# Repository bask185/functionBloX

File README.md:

# Function block programming 4 Arduinoy

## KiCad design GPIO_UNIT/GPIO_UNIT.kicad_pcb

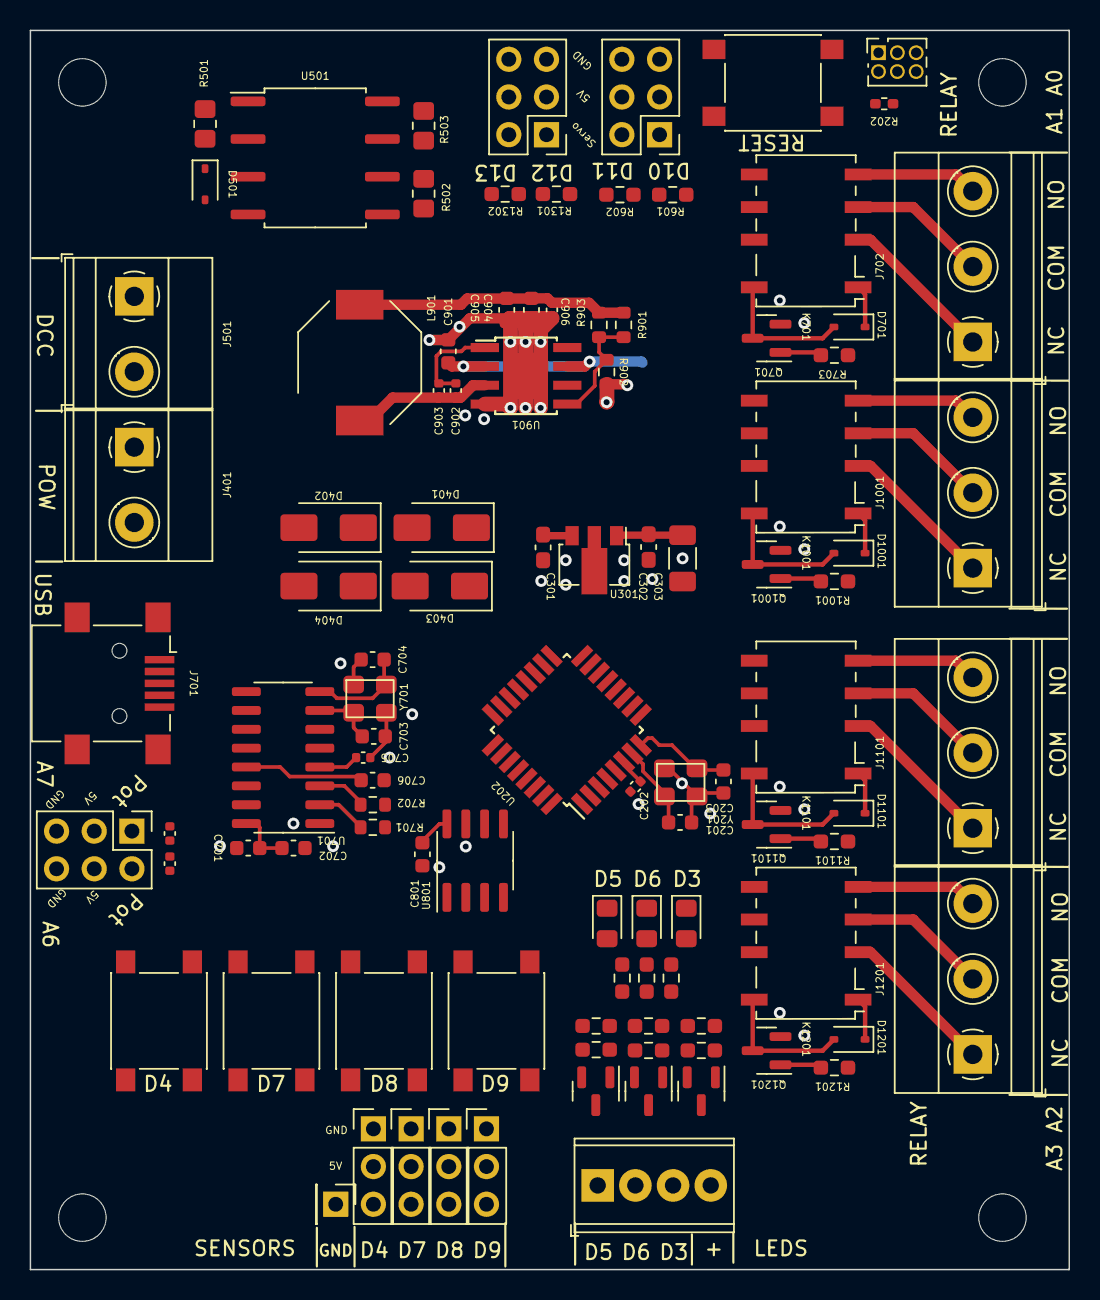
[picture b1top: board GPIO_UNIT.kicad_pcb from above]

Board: 2 copper layers, 70.0 x 83.5 mm, 101 parts (0 on the bottom side), 75 nets.

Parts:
C201, C203: 12pF; C_0603_1608Metric
C202, C705, C902, C906, C1401, C1402: 100nF; C_0402_1005Metric
C301: 330nF; C_0603_1608Metric_Pad1.08x0.95mm_HandSolder
C302: 100nF; C_0603_1608Metric_Pad1.08x0.95mm_HandSolder
C303: 100uF; C_1206_3216Metric_Pad1.33x1.80mm_HandSolder
C701: 10uF; C_0603_1608Metric
C702, C706, C801: 100nF; C_0603_1608Metric
C703, C704: 22pF; C_0603_1608Metric
C901, C904, C905: 22uF; C_0603_1608Metric
C903: 22nF; C_0402_1005Metric
D401, D402, D403, D404: SS53; D_SMA
D501, D701, D1001, D1101, D1201: 1N4148WS; D_SOD-323
D901, D902, D903: LED; LED_0805_2012Metric_Pad1.15x1.40mm_HandSolder
J401, J501: Screw_Terminal_01x02; TerminalBlock_Phoenix_MKDS-1,5-2-5.08_1x02_P5.08mm_Horizont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
J601, J1301, J1401: Conn_02x03_Odd_Even; PinHeader_2x03_P2.54mm_Vertical
J701: USB_B_Mini; USB_Mini-B_Lumberg_2486_01_Horizontal
J702, J1001, J1101, J1201: Screw_Terminal_01x03; TerminalBlock_Phoenix_MKDS-1,5-3-5.08_1x03_P5.08mm_Horizont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
J802, J803, J804, J805: Conn_01x03_Pin; PinHeader_1x03_P2.54mm_Vertical
J806: Conn_01x01_Pin; PinHeader_1x01_P2.54mm_Vertical
J901: Screw_Terminal_01x04; TerminalBlock_Phoenix_MPT-0,5-4-2.54_1x04_P2.54mm_Horizontal
K701, K1001, K1101, K1201: G6K-2F-Y-TR DC5; Relay_DPDT_Omron_G6K-2F-Y
L901: L; L_Bourns-SRU8028_8.0x8.0mm
Q701, Q1001, Q1101, Q1201: NPN_TOR; SOT-23
Q901, Q902, Q903: AO3400A; SOT-23
R202: 10k; R_0402_1005Metric_Pad0.72x0.64mm_HandSolder
R501: 1k; R_0805_2012Metric_Pad1.20x1.40mm_HandSolder
R502, R503: 10k; R_0805_2012Metric_Pad1.20x1.40mm_HandSolder
R601, R602, R1301, R1302: 10k; R_0603_smalltext
R701, R702: 1k; R_0603_1608Metric
R703, R1001, R1101, R1201: 1k; R_0603_smalltext
R901: 220k; R_0603_1608Metric
R902: 20k; R_0603_1608Metric
R903: 150k; R_0603_1608Metric
R904, R905, R906: 22R; R_0603_smalltext
R907, R908, R909: 3k3; R_0603_smalltext
R910, R911, R912: 22k; R_0603_smalltext
SW202, SW801, SW802, SW803, SW804: SW_Push; tactile_SMD_6mm
U201: HEADER_3x2; PinSocket_2x03_P1.27mm_Vertical
U202: ATmega328-A; TQFP-32_7x7mm_P0.8mm
U301: L78L05_SOT89; SOT-89-3
U501: 6N137; SOP-8_6.62x9.15mm_P2.54mm
U701: CH340G; SOIC-16_3.9x9.9mm_P1.27mm
U801: 24LC256; SOIC-8_3.9x4.9mm_P1.27mm
U901: MT2499A; TI_SO-PowerPAD-8
Y201: Crystal_GND2; crystal_arduino
Y701: Crystal; crystal_arduino

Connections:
+5V: C202.1, C302.1, C303.1, C701.1, C702.1, C801.2, C1401.1, C1402.2, J701.1 (VBUS), J802.2, J803.2, J804.2, J805.2, J1401.3, J1401.4, R202.1, R502.1, R503.1, R601.2, R602.2, R1301.2, R1302.2, U201.5, U202.4 (VCC), U202.6 (VCC), U202.18 (AVCC), U301.1 (OUT), U501.8 (VCC), U701.16 (VCC), U801.8 (VCC)
+5VA: C904.1, C905.1, C906.1, D701.1 (K), D1001.1 (K), D1101.1 (K), D1201.1 (K), J601.3, J601.4, J1301.3, J1301.4, K701.1, K1001.1, K1101.1, K1201.1, L901.2, R901.1, R903.2
/CPU/X1: C201.2, U202.7 (XTAL1/PB6), Y201.1
/CPU/X2: C203.2, U202.8 (XTAL2/PB7), Y201.3
/DCC: R503.2, U202.32 (PD2), U501.6 (VO)
/L1: R904.1, R907.2, U202.1 (PD3)
/L2: R905.1, R908.2, U202.9 (PD5)
/L3: R906.1, R909.2, U202.10 (PD6)
/P1: C1402.1, J1401.2, U202.19 (ADC6), U202.22 (ADC7)
/P2: C1401.2, J1401.1
/R1: R703.1, U202.23 (PC0)
/R2: R1001.1, U202.24 (PC1)
/R3: R1101.1, U202.25 (PC2)
/R4: R1201.1, U202.26 (PC3)
/Rx: R701.2, U202.30 (PD0)
/S1: J601.1, R601.1, U202.14 (PB2)
/S2: J601.2, R602.1, U201.3, U202.15 (PB3)
/S3: J1301.1, R1301.1, U201.6, U202.16 (PB4)
/S4: J1301.2, R1302.1, U201.4, U202.17 (PB5)
/SCL: U202.28 (PC5), U801.6 (SCL)
/SDA: U202.27 (PC4), U801.5 (SDA)
/SW1: J802.3, SW801.1, U202.2 (PD4)
/SW2: J803.3, SW802.1, U202.11 (PD7)
/SW3: J804.3, SW803.1, U202.12 (PB0)
/SW4: J805.3, SW804.1, U202.13 (PB1)
/Tx: R702.1, U202.31 (PD1)
/reset: C706.2, R202.2, SW202.2, U201.2
GND: C201.1, C202.2, C203.1, C301.2, C302.2, C303.2, C701.2, C702.2, C703.2, C704.2, C705.1, C801.1, C901.2, C904.2, C905.2, C906.2, D402.2 (A), D404.2 (A), D901.1 (K), D902.1 (K), D903.1 (K), J601.5, J601.6, J701.5 (GND), J701.6 (Shield), J802.1, J803.1, J804.1, J805.1, J806.1, J1301.5, J1301.6, J1401.5, J1401.6, Q701.2 (E), Q901.2 (S), Q902.2 (S), Q903.2 (S), Q1001.2 (E), Q1101.2 (E), Q1201.2 (E), R902.2, R910.2, R911.2, R912.2, SW202.1, SW801.2, SW802.2, SW803.2, SW804.2, U201.1, U202.3 (GND), U202.5 (GND), U202.21 (GND), U301.2 (GND), U501.5 (GND), U701.1 (GND), U801.1 (A0), U801.2 (A1), U801.3 (A2), U801.4 (GND), U801.7 (WP), U901.4 (GND), U901.9 (GND), Y201.2 (GND), Y201.4 (GND), Y701.2 (GND), Y701.4 (GND)
unnamed: D401.2 (A), D402.1 (K), J401.1
unnamed: D403.2 (A), D404.1 (K), J401.2
unnamed: D501.2 (A), J501.2, U501.3 (C)
unnamed: D501.1 (K), R501.2, U501.2 (A)
unnamed: D701.2 (A), K701.8, Q701.3 (C)
unnamed: D901.2 (A), R907.1
unnamed: D902.2 (A), R908.1
unnamed: D903.2 (A), R909.1
unnamed: D1001.2 (A), K1001.8, Q1001.3 (C)
unnamed: D1101.2 (A), K1101.8, Q1101.3 (C)
unnamed: D1201.2 (A), K1201.8, Q1201.3 (C)
unnamed: J501.1, R501.1
unnamed: J701.3 (D+), U701.5 (UD+)
unnamed: J701.2 (D-), U701.6 (UD-)
unnamed: J702.1, K701.2
unnamed: J702.2, K701.3
unnamed: J702.3, K701.4
unnamed: J901.1, Q903.3 (D)
unnamed: J901.2, Q902.3 (D)
unnamed: J901.3, Q901.3 (D)
unnamed: J1001.1, K1001.2
unnamed: J1001.2, K1001.3
unnamed: J1001.3, K1001.4
unnamed: J1101.1, K1101.2
unnamed: J1101.2, K1101.3
unnamed: J1101.3, K1101.4
unnamed: J1201.1, K1201.2
unnamed: J1201.2, K1201.3
unnamed: J1201.3, K1201.4
unnamed: Q701.1 (B), R703.2
unnamed: Q901.1 (G), R904.2, R910.1
unnamed: Q902.1 (G), R905.2, R911.1
unnamed: Q903.1 (G), R906.2, R912.1
unnamed: Q1001.1 (B), R1001.2
unnamed: Q1101.1 (B), R1101.2
unnamed: Q1201.1 (B), R1201.2
unnamed: R502.2, U501.7 (EN)
unnamed: R702.2, U701.3 (RXD)
unnamed: R701.1, U701.2 (TXD)
unnamed: C705.2, U701.4 (V3)
unnamed: C703.1, U701.7 (XI), Y701.1
unnamed: C704.1, U701.8 (XO), Y701.3
unnamed: C706.1, U701.13 (~DTR)
unnamed: C902.1, C903.1, U901.1 (BS)
unnamed: R901.2, R902.1, R903.1, U901.5 (FB)
unnamed: C902.2, C903.2, L901.1, U901.3 (SW)
VCC: C301.1, C901.1, D401.1 (K), D403.1 (K), J901.4, U301.3 (IN), U901.2 (Vin), U901.7 (EN)

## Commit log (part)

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2022-09-15 Added input and output blocks which are not yet functional. If these become operational the basics should work.
    Function blocks and links are ok
2022-09-15 input/output numbers work in processing, but the arduino source code is to be altered with the pinnumbers.
    The first test with manipulating IO via serial port seems to actually work. Both Memory, AND and OR gates seem to actually work
2022-09-16 The very basiscs should be operational with exception of the delay. Code must be tested with real hardware.
    Storing and loading layouts are next in line
2022-09-19 saving the funcion blocks and links work, loading the blocks also work, loading links are yet to be done
2022-09-20 both saving and loading the layout seem to work well now
2022-09-20 fixed a bug with which the links' INs would not be properly initialized (forgot break statements in switch-case)
2022-09-23 rebuilt the arduino code to work with subclassed. The delay block actually works but I still need a method to enter a number for a delay time. The arduino code has it's own heade file to simplify the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
2022-09-23 fixed a minor bug which would render the program inoperable if the very last FB was removed. If there are now no blocks, the texts appear to be in operable.
    Next stuff in line is to new blocks like a pulse generator, JK flip flop, decade counter perhaps?
2022-09-23 added JK flip flop as well as a checklist for adding new components
2022-09-25 analog input and output added. Links are not yet ready. The Link class needs a new boolean set to indicate it is an analog link analog links will use ana_Q and ana_IN instead Q and In respectively. T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
2022-09-25 did some work on the analog link. Loading and saving analog links must be tested
2022-09-26 I am going to alter the formation of links. Indices must be calculated depending on the amount of digital and analog blocks
2022-09-26 did a lot of work to the links. Begin and end coordinates are checked at all times to update Q and IN. If a block is replaced by another the link get updated automatically.. well it should, it is not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
2022-09-26 the first analog link has been set. It seems to work well. The automatic updating of links partially works but contains bugs. I also need to cross analog and digital connections
2022-09-27 added remaining subclasses to the arduino project and I altered the assembly of the arduino program. All blocks are implemented there. Only the servo objects must be initialized. I also want to try t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
2022-09-27 added several new function blocks for the test. Take note that the program does not want to compile on an unknown rule
2022-09-27 Fixed the compile bug. A } was missing. The new components appear to work in processing
2022-09-27 minor update to the TODO list
2022-09-27 added base for zooming in n out
2022-09-27 some outlining, commit for going home
2022-09-28 Upgraded the delay block from digital to analog. The reason is that this allows a delay to slowly increment or decrement it's Q to follow it's IN. This is usefull to let a servo motor move slowly by 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
2022-09-28 shortened the connection lines so lines of adjacent blocks do not touch eachother anymore. It looked like adjacent blocks were connected when they werent. I also added comperator to processing and I 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
2022-09-28 added a constant to both processing as arduino, but I really should not use it in arduino as it squanders 12 bytes of memory instead of 0 bytes
2022-09-28 altered the link class to accomodate special variable for digital/analog inputs and outputs. This allows for mixed link between analog and digitial components. The main file needs to be altered for t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
2022-09-28 finished the part of the links so analog and digital links can be made in the arduino program. Now I need to merge with.
2022-09-28 added colors, but not yet with constants. About to add setting the map values
2022-09-28 added functionality to store and load the map values
2022-09-28 fixed missing texts. All texts are now correct and every block can be safed and loaded
2022-09-28 commit for push
2022-09-28 The links in the arduino can now be mixed analog and digital. Every link knows whatever it's Q and In is. An exception is the comperator. But it does not really matter
2022-09-29 minor improvements. commit for pull
2022-09-29 The constant value has been fixed, but the constant function block screws up all indices. Storing of the links also need to be fixed. Currently the stop positions are not well stored/loaded.
2022-09-29 I used conventional constant blocks for the time being. This allow me to test the remainder of the program. It seems to work well The thing I really lack is that I cannot enter texts for serial block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
2022-09-29 added the 3 primary control buttons (all working). Refactored the printTexts function
2022-10-01 added code to help navigate through all functions. About to add the servo initialisation.
2022-10-01 The servo initialisation should work. It is not yet tested. I also refactored the code a little and added a comment guide in order to navigate through all functions. The last thing to do is to add th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
2022-10-02 Added adding texts. The basis is there, but it needs much love.
2022-10-03 added the controlButton.pde to the repo
2022-10-03 I may have fixed the bug where an item with type 37 was added as last item, despite it doesnt exist. The serial blocks are working. But editting in the program is not yet right
2022-10-04 added the loading and saving from text, unsure if it works or not
2022-10-04 added some comments
2022-10-04 made sure than all analog blocks are treated as analog blocks by the links. The new block were recognizes as digital blocks casuing faulty links
2022-10-04 added a clearProgram button which works
2022-10-04 Added rising, falling and arithmatic FB to processing
2022-10-04 added arithmatic, falling and rising edge FB to arduino program. falling/rising edges have been tested using function generator. All blocks must be added to processing
2022-10-04 made sure that no false FB can be added. The works should be different, I am now just checking if mouseY is less than height - 5x60.. If I add blocks I must alter this..
2022-10-04 altered serial in block so that message is received after a new line. All non printables but \n are discarded entirely
2022-10-04 code has somewhat been reformatted. The demo blocks have a new boolean in order to determen the mouse is hovering over one
2022-10-05 Panning appears to work, but only as long as you don't place or move items around while having an offset. I am thinking to ditch panning and zooming all togahter.. but I would like to keep it..
2022-10-05 instead of altering the display coordinates (which breaks the entire program) I simply add the offsets to xPos and Ypos in updateCursor. The links pan just fine, the function blocks dont seem to care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
2022-10-05 added export.sh script to help assembly binary and copy the needed files to launche the binary. The binary does look fucked up though... fullscreen does not cut it
2022-10-06 altered export.sh and removed the debug texts for release
2022-10-11 altered servo motors to work with an optional latch pin and the motor will be detached automatically if it's position does not change for 500ms
2022-10-12 added vertical and horizontal lines which snap to the grid. This makes it much more easier to draw the links between blocks
2022-10-12 First official release.
2022-10-13 changed that a mouseclick will jump to idle if one was altering a number or text. It was kinda annoying that the program would "freeze" if you accidently clicked a changeable thing
2022-10-14 commit for merge
2022-10-14 I have loading and saving files working well. Only the quit button no longer saves
2022-10-15 - enabled zooming with middle mousewheel (N.B. panning does not work) - adjustable numbers like pin numbers and times are now visable in the texts on top of the display - loading and saving files of 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
2023-04-29 added NMRA dcc library
2023-04-29 The DCC function block seems to work. But the actual DCC signal as input is not tested. The DCC library should not toss a timer conflict, killing servo operations.
2023-04-30 DCC code is succesfully tested with hardware. All bugs have been resolved and the code is backward compatible with older csv files.
2023-05-09 altered code to work with long type variable for delay time and map block values. Had to do alot of casting
2023-12-14 trying to launch batch file from application, but it does not yet work
2023-12-19 FunctionBloX is now able to use arduino-cli to determen if a board is connected, what it's fqbn is and what comport number is assigned. FuncTionBLoX can also compile and flash to the arduino board wi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
    TODO:
    - chinese clones (boards with ch340 chips) must be tested with this. Unsure if this handshaking is part of bootloader, serial usb chip or both.
    - build and upload status should be displayed on main screen.
    - I should investigate if a rudimentary serial monitor can be added. It would sorta be neat if you can issue commands to the arduino from within FunctionBlox.
    additionally control button could be added which may send strings of choise. Than user
2023-12-21 Need to test with ch340 chips and devise a method to get the right com port. I have selection boxes for UNO, NANO and MEGA. They work but they override the fqbn if an original arduino is plugged in. 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
    A com port text and dummy number is added. But it is not yet in use. Method is needed to list all com ports found by arduino-cli.
    it would be neat if an event can be triggered when an arduino is plugged in
    Also added name of program and me logo
2023-12-21 flashing program function has been simplified. Finding comport should work, always as a search is done for 'USB' I have been using more method chaining to simplify things.
    todo.
    warning or message that a board must be selected
2024-01-04 added missing files
2024-01-04 added empty sketchbook folder and numerous example programs
2024-01-08 added configuration files for arduino cli
2024-01-08 Digital pins are now able to use the analog pinnumbering as well. Pin can be set to an analog or digital pin number by simply pressing a or d respectively when editting the pinnumbers. Take note that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
2024-01-08 added 2 default sketch projects. They seem to lack extensions? Unclear if this matters or not. It seems not
2024-01-08 due to different processing versions I added the settings function. It is here where size() should be called.
2024-01-08 made minor cosmetic changes and added the nano with old bootloader as option. It does look crap tho... perhaps fix this one day to have separate name and fqbn
2024-01-18 added GPIO UNIT board. To be renamed Jack Of All trades
2024-03-11 relocated board files 'elsewhere'.
    Finally panning works.. mostly. I still have to do the link locations.
    As is now I added limits to drawing the function blocks. But I'd rather redo the background drawing in 2 parts. Not yet sure.
    The links and nodes need to return the offset positions like the function blocks do.
2024-03-13 added missing Text.pde
2024-03-13 made some changes and some bug fixes. Update links is now only done when program is assembled. Should save me some processing power
2024-03-13 with exception of serial text bug, the code seems to be operational. The export folder need to be tested now
2024-03-18 Relocated the train-science image to apropiate folder.
    Debugged the download tool. Now changes will be pushed to the arduino in the first iteration
2024-03-18 Added a start up delay of 50ms to all output type function blocks to prevent illegal outputs during first program cycles
